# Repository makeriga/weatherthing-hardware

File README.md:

# weatherthing-hardware
hardware for WeatherThing LED matrix
R0 PCB source files and mech parts + manual pdf
Note: R0 pcb somehow no one paid attention to the 1117 LDO Vin low voltage, thus the battery charging, protection and power path section kinda became redundant. Pls omit or DNP those parts.

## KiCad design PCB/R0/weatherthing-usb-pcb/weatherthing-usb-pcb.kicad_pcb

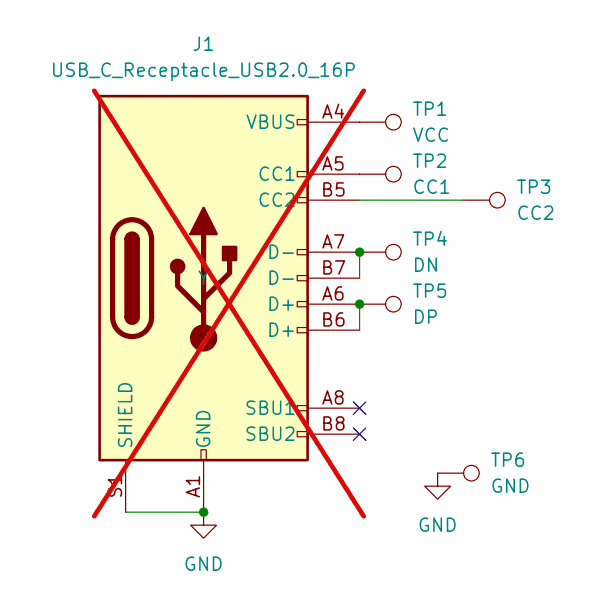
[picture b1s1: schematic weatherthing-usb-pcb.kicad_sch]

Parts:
J1: USB_C_Receptacle_USB2.0_16P; USB_C_Receptacle_GCT_USB4105-xx-A_16P_TopMnt_Horizontal; not fitted
TP1: VCC; pad-28-35
TP2: CC1; pad-28-35
TP3: CC2; pad-28-35
TP4: DN; pad-28-35
TP5: DP; pad-28-35
TP6: GND; pad-28-35

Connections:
GND: J1.A1 (GND), J1.A12 (GND), J1.B1 (GND), J1.B12 (GND), J1.S1 (SHIELD), TP6.1
unnamed: J1.A5 (CC1), TP2.1
unnamed: J1.B5 (CC2), TP3.1
unnamed: J1.A6 (D+), J1.B6 (D+), TP5.1
unnamed: J1.A7 (D-), J1.B7 (D-), TP4.1
unnamed: J1.A4 (VBUS), J1.A9 (VBUS), J1.B4 (VBUS), J1.B9 (VBUS), TP1.1

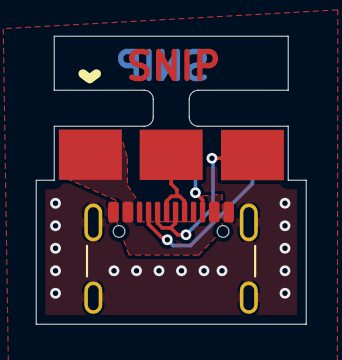
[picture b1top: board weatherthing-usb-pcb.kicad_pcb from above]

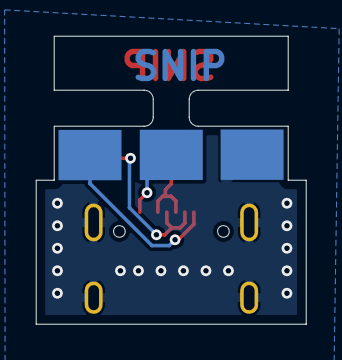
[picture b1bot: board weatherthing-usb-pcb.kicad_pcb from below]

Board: 2 copper layers, 15.0 x 16.0 mm, 7 parts (3 on the bottom side), 6 nets.

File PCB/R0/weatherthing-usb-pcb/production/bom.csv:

Designator,Footprint,Quantity,Value,LCSC Part #
J1,USB_C_Receptacle_GCT_USB4105-xx-A_16P_TopMnt_Horizontal,1,USB_C_Receptacle_USB2.0_16P,
TP1,pad-28-35,1,VCC,
TP2,pad-28-35,1,CC1,
TP3,pad-28-35,1,CC2,
TP4,pad-28-35,1,DN,
TP5,pad-28-35,1,DP,
TP6,pad-28-35,1,GND,
